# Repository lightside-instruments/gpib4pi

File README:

The gpib4pi project is open hardware design of a Raspbery Pi
extension board with GPIB interface using only GPIOs.

The project includes schematics and PCB
design files for KiCAD. The board can be used with
the linux-gpib software tools and the gpib_bitbang.ko
driver.

The project is published by Lightside Instruments AS
under TAPR Open Hardware License. Read the LICENSE file
for details.

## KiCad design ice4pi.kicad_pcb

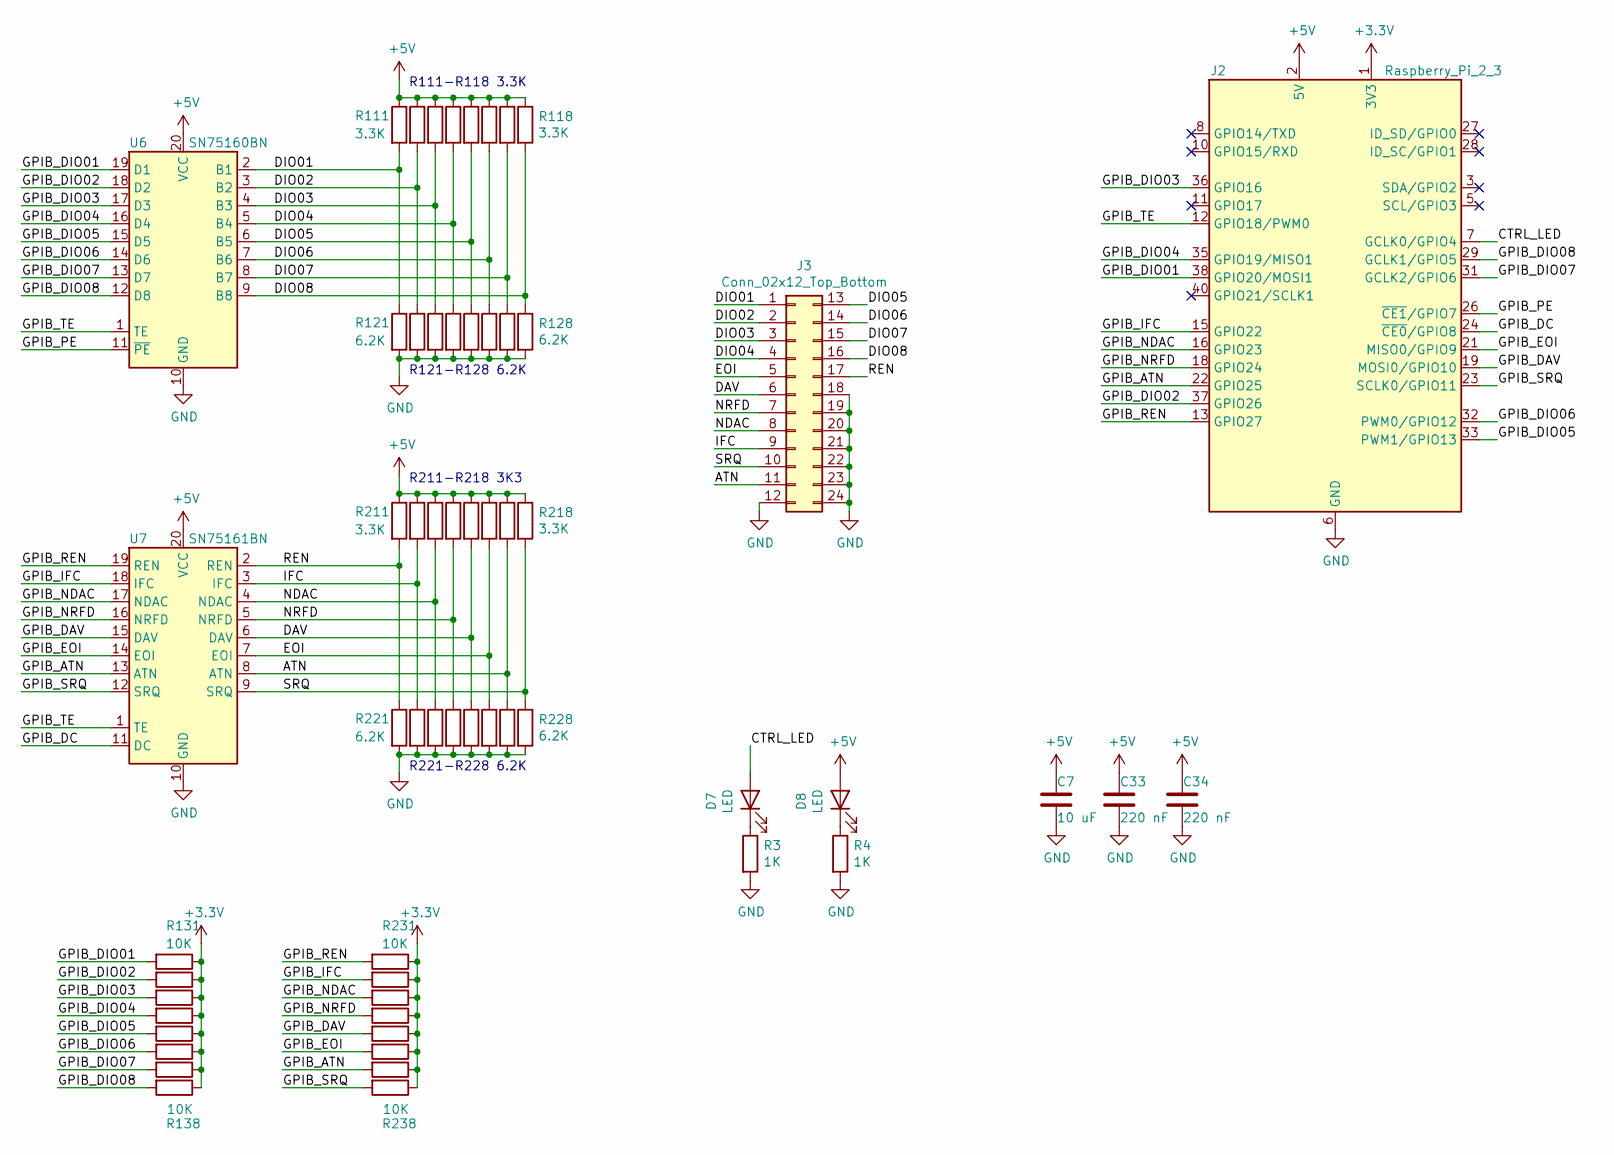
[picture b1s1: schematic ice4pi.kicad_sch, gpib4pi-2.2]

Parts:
C7: 10 uF; C_0402_1005Metric
C33, C34: 220 nF; C_0402_1005Metric
D7, D8: LED; LED_0603_1608Metric
J2: Raspberry_Pi_2_3; PinSocket_2x20_P2.54mm_Vertical_1_04mm
J3: Conn_02x12_Top_Bottom; centronix-24-male
R3, R4: 1K; R_0402_1005Metric
R111, R112, R113, R114, R115, R116, R117, R118, R132, R211, R212, R213, R214, R215, R216, R217, R218, R232: 3.3K; R_0402_1005Metric
R121, R122, R123, R124, R125, R126, R127, R128, R221, R222, R223, R224, R225, R226, R227, R228: 6.2K; R_0402_1005Metric
R131, R133, R134, R135, R136, R137, R138, R231, R233, R234, R235, R236, R237, R238: 10K; R_0402_1005Metric
U6: SN75160BN; DIP-20_W7.62mm
U7: SN75161BN; DIP-20_W7.62mm

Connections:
+3.3V: J2.1 (3V3), J2.17 (3V3), R131.1, R132.1, R133.1, R134.1, R135.1, R136.1, R137.1, R138.1, R231.1, R232.1, R233.1, R234.1, R235.1, R236.1, R237.1, R238.1
+5V: C7.1, C33.1, C34.1, D8.2 (A), J2.2 (5V), J2.4 (5V), R111.1, R112.1, R113.1, R114.1, R115.1, R116.1, R117.1, R118.1, R211.1, R212.1, R213.1, R214.1, R215.1, R216.1, R217.1, R218.1, U6.20 (VCC), U7.20 (VCC)
/ATN: J3.11, R217.2, R227.1, U7.8 (ATN)
/CTRL_LED: D7.2 (A), J2.7 (GCLK0/GPIO4)
/DAV: J3.6, R215.2, R225.1, U7.6 (DAV)
/DIO01: J3.1, R111.2, R121.1, U6.2 (B1)
/DIO02: J3.2, R112.2, R122.1, U6.3 (B2)
/DIO03: J3.3, R113.2, R123.1, U6.4 (B3)
/DIO04: J3.4, R114.2, R124.1, U6.5 (B4)
/DIO05: J3.13, R115.2, R125.1, U6.6 (B5)
/DIO06: J3.14, R116.2, R126.1, U6.7 (B6)
/DIO07: J3.15, R117.2, R127.1, U6.8 (B7)
/DIO08: J3.16, R118.2, R128.1, U6.9 (B8)
/EOI: J3.5, R216.2, R226.1, U7.7 (EOI)
/GPIB_ATN: J2.22 (GPIO25), R237.2, U7.13 (ATN)
/GPIB_DAV: J2.19 (MOSI0/GPIO10), R235.2, U7.15 (DAV)
/GPIB_DC: J2.24 (~CE0/GPIO8), U7.11 (DC)
/GPIB_DIO01: J2.38 (GPIO20/MOSI1), R131.2, U6.19 (D1)
/GPIB_DIO02: J2.37 (GPIO26), R132.2, U6.18 (D2)
/GPIB_DIO03: J2.36 (GPIO16), R133.2, U6.17 (D3)
/GPIB_DIO04: J2.35 (GPIO19/MISO1), R134.2, U6.16 (D4)
/GPIB_DIO05: J2.33 (PWM1/GPIO13), R135.2, U6.15 (D5)
/GPIB_DIO06: J2.32 (PWM0/GPIO12), R136.2, U6.14 (D6)
/GPIB_DIO07: J2.31 (GCLK2/GPIO6), R137.2, U6.13 (D7)
/GPIB_DIO08: J2.29 (GCLK1/GPIO5), R138.2, U6.12 (D8)
/GPIB_EOI: J2.21 (MISO0/GPIO9), R236.2, U7.14 (EOI)
/GPIB_IFC: J2.15 (GPIO22), R232.2, U7.18 (IFC)
/GPIB_NDAC: J2.16 (GPIO23), R233.2, U7.17 (NDAC)
/GPIB_NRFD: J2.18 (GPIO24), R234.2, U7.16 (NRFD)
/GPIB_PE: J2.26 (~CE1/GPIO7), U6.11 (~PE)
/GPIB_REN: J2.13 (GPIO27), R231.2, U7.19 (REN)
/GPIB_SRQ: J2.23 (SCLK0/GPIO11), R238.2, U7.12 (SRQ)
/GPIB_TE: J2.12 (GPIO18/PWM0), U6.1 (TE), U7.1 (TE)
/IFC: J3.9, R212.2, R222.1, U7.3 (IFC)
/NDAC: J3.8, R213.2, R223.1, U7.4 (NDAC)
/NRFD: J3.7, R214.2, R224.1, U7.5 (NRFD)
/REN: J3.17, R211.2, R221.1, U7.2 (REN)
/SRQ: J3.10, R218.2, R228.1, U7.9 (SRQ)
GND: C7.2, C33.2, C34.2, J2.6 (GND), J2.9 (GND), J2.14 (GND), J2.20 (GND), J2.25 (GND), J2.30 (GND), J2.34 (GND), J2.39 (GND), J3.12, J3.18, J3.19, J3.20, J3.21, J3.22, J3.23, J3.24, R3.2, R4.2, R121.2, R122.2, R123.2, R124.2, R125.2, R126.2, R127.2, R128.2, R221.2, R222.2, R223.2, R224.2, R225.2, R226.2, R227.2, R228.2, U6.10 (GND), U7.10 (GND)
unnamed: D7.1 (K), R3.1
unnamed: D8.1 (K), R4.1

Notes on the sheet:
R111-R118 3.3K
R121-R128 6.2K
R211-R218 3K3
R221-R228 6.2K

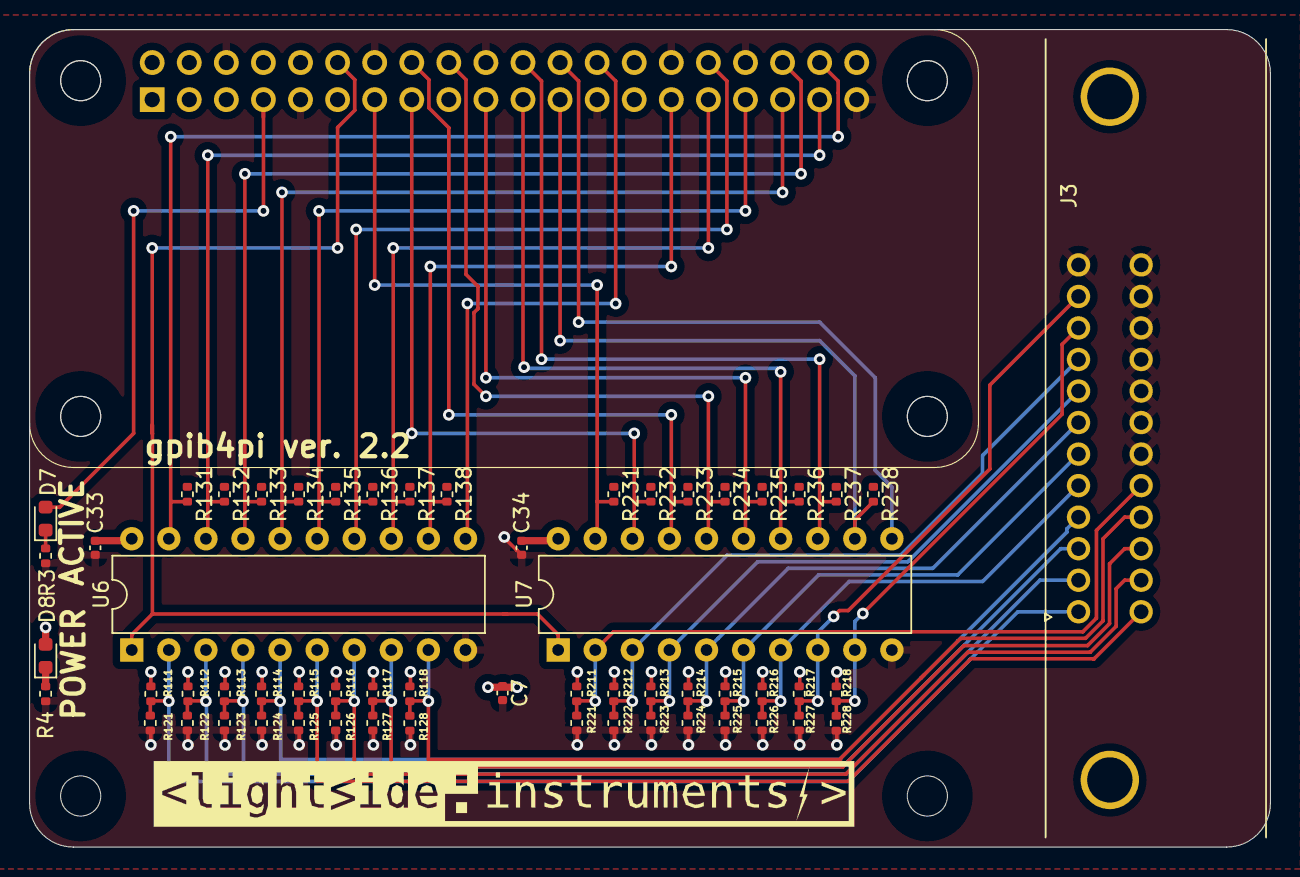
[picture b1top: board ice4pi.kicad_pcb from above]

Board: 4 copper layers, 85.0 x 56.0 mm, 60 parts (1 on the bottom side), 41 nets.

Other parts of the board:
svg2mod: G***; lsi-logo-48mm

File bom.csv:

Reference,Quantity,Identifier,footprint,Value,Tolerance,Voltage,Current,Power,PN
J2,1,,ice4pi:PinSocket_2x20_P2.54mm_Vertical_1_04mm,Raspberry_Pi_2_3,,,,,SSW-120-01-T-D-006
J3,1,,ice4pi:centronix-24-male,Conn_02x12_Top_Bottom,,,,,112-024-113R001
U6,1,,Package_DIP:DIP-20_W7.62mm,SN75160BN,,,,,SN75160BN 
U7,1,,Package_DIP:DIP-20_W7.62mm,SN75161BN,,,,,SN75161BN 
R111-R118;R211-R218,16,,Resistor_SMD:R_0402_1005Metric,3.3K,,,,,RC0402JR-073K3L
R121-R128;R221-R228,16,,Resistor_SMD:R_0402_1005Metric,6.2K,,,,,RC0402FR-076K2L
R131-R138;R231-R238,16,,Resistor_SMD:R_0402_1005Metric,10K,,,,,RC0402JR-0710KL
"C33,C34",2,,Capacitor_SMD:C_0402_1005Metric,220nF,,,,,GRM155C8YA224KE01J
C7,1,,Capacitor_SMD:C_0402_1005Metric,10uF,,,,,ZRB15XR61A106ME01D
"R3,R4",2,,Resistor_SMD:R_0402_1005Metric,1K,,,,,ERJ-2GEJ102X 
D7,1,,Diode_SMD:D_0603_1608Metric,ACTIVE_LED_GREEN,,,,,150060VS55040
D8,1,,Diode_SMD:D_0603_1608Metric,POWER_LED_RED,,,,,150060RS55040

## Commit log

2020-01-29 Release ice4pi-1.0
2020-02-14 Release ice4pi-1.1
2020-02-14 Errata ice4pi-1.1-1
2021-01-29 Release 1.2
2022-02-04 Release ice4pi-gpib-1.0
2022-02-05 Release gpib4pi-1.0
2022-08-08 Release gpib4pi-1.1
2023-02-14 Release gpib4pi-1.2
2023-02-14 Release gpib4pi-2.0
2023-02-16 Release gpib4pi-2.1
2025-01-30 Release gpib4pi-2.2-experimental-pullup
